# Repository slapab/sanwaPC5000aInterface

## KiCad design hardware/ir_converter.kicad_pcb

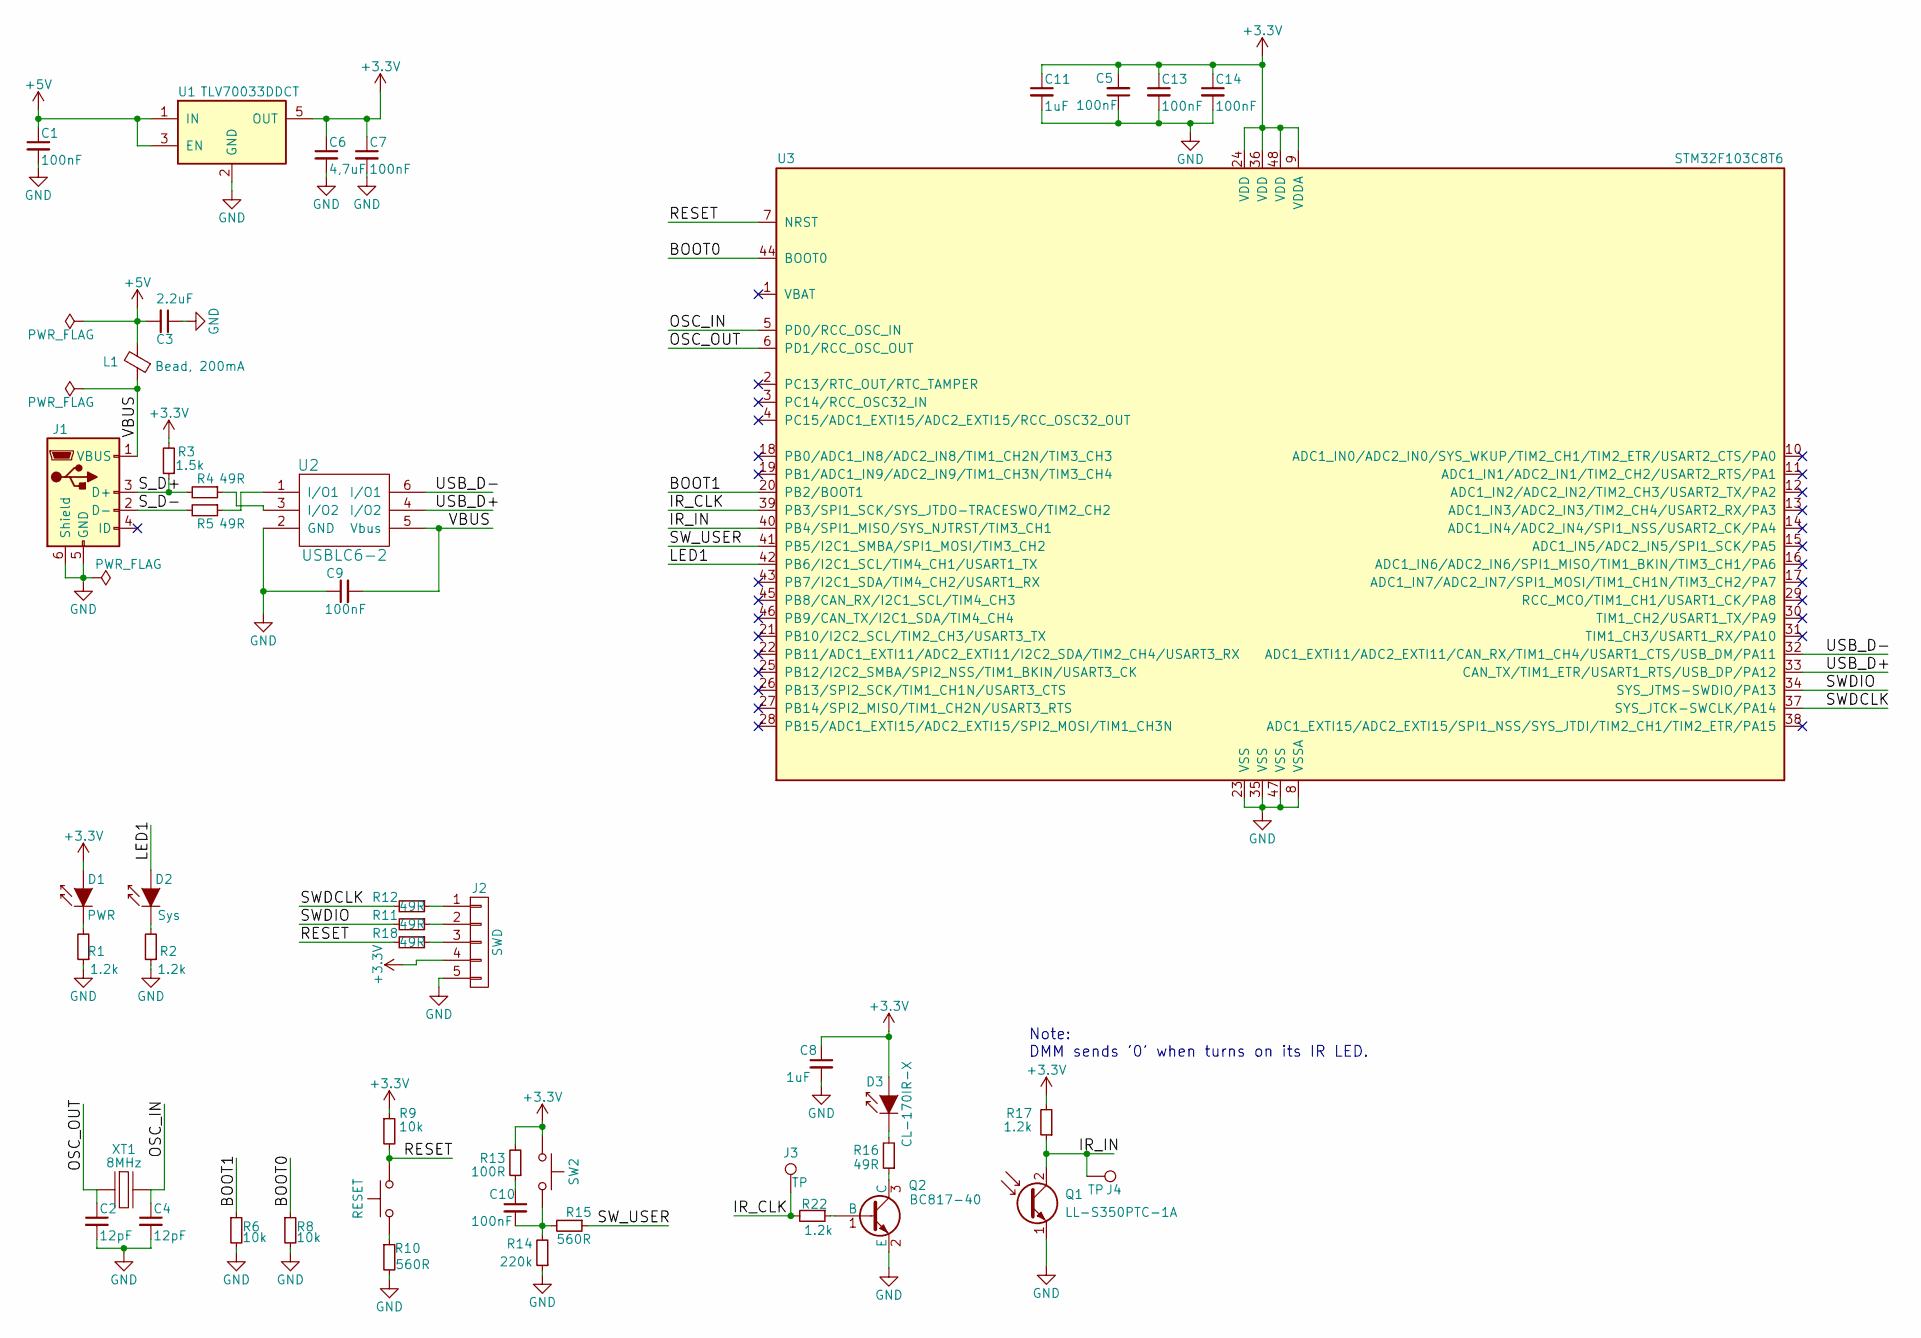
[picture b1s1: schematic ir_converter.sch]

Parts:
C1, C5, C7, C9, C10, C13, C14: 100nF; C_0603_HandSoldering
C2, C4: 12pF; C_0603_HandSoldering
C3: 2.2uF; C_0805_HandSoldering
C6: 4,7uF; C_0603_HandSoldering
C8, C11: 1uF; C_0603_HandSoldering
D1: PWR; LED_1206
D2: Sys; LED_1206
D3: CL-170IR-X; IR_LED_WIDE
J1: MX-47346-0001; USB_MICRO_MX-47346-0001
J2: SWD; Pin_Header_Straight_1x05_Pitch2.54mm
J3, J4: TP; Measurement_Point_Square-SMD-Pad_Small
L1: Bead, 200mA; L_1206_Handsoldering
Q1: LL-S350PTC-1A; IR_PHOTO_WIDE
Q2: BC817-40; SOT-23
R1, R2, R17, R22: 1.2k; R_0603_HandSoldering
R3: 1.5k; R_0603_HandSoldering
R4, R5, R11, R12, R16, R18: 49R; R_0603_HandSoldering
R6, R8, R9: 10k; R_0603_HandSoldering
R10, R15: 560R; R_0603_HandSoldering
R13: 100R; R_0603_HandSoldering
R14: 220k; R_0603_HandSoldering
SW1: RESET; SW_SPST_FSMSM
SW2: SW2; SW_SPST_FSMSM
U1: TLV70033DDCT; SOT-23-5
U2: USBLC6-2; SOT-23-6_Handsoldering
U3: STM32F103C8T6; LQFP-48_7x7mm_Pitch0.5mm
XT1: 8MHz; Crystal_SMD_HC49-SD

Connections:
+3V3: C5.2, C6.1, C7.1, C8.1, C11.1, C13.1, C14.1, D1.2 (A), D3.2 (A), J2.4, R3.2, R9.1, R13.2, R17.2, SW2.1, U1.5 (OUT), U3.9 (VDDA), U3.24 (VDD), U3.36 (VDD), U3.48 (VDD)
+5V: C1.1, C3.2, L1.2, U1.1 (IN), U1.3 (EN)
/BOOT0: R8.1, U3.44 (BOOT0)
/BOOT1: R6.1, U3.20 (PB2/BOOT1)
/IR_CLK: J3.1, R22.2, U3.39 (PB3/SPI1_SCK/SYS_JTDO-TRACESWO/TIM2_CH2)
/IR_IN: J4.1, Q1.2 (C), R17.1, U3.40 (PB4/SPI1_MISO/SYS_NJTRST/TIM3_CH1)
/LED1: D2.2 (A), U3.42 (PB6/I2C1_SCL/TIM4_CH1/USART1_TX)
/OSC_IN: C4.1, U3.5 (PD0/RCC_OSC_IN), XT1.2
/OSC_OUT: C2.1, U3.6 (PD1/RCC_OSC_OUT), XT1.1
/RESET: R9.2, R18.2, SW1.2, U3.7 (NRST)
/SWDCLK: R12.2, U3.37 (SYS_JTCK-SWCLK/PA14)
/SWDIO: R11.2, U3.34 (SYS_JTMS-SWDIO/PA13)
/SW_USER: R15.1, U3.41 (PB5/I2C1_SMBA/SPI1_MOSI/TIM3_CH2)
/S_D+: J1.3 (D+), R3.1, R4.2
/S_D-: J1.2 (D-), R5.2
/USB_D+: U2.4 (I/O2), U3.33 (CAN_TX/TIM1_ETR/USART1_RTS/USB_DP/PA12)
/USB_D-: U2.6 (I/O1), U3.32 (ADC1_EXTI11/ADC2_EXTI11/CAN_RX/TIM1_CH4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)
/VBUS: C9.2, J1.1 (VBUS), L1.1, U2.5 (Vbus)
GND: C1.2, C2.2, C3.1, C4.2, C5.1, C6.2, C7.2, C8.2, C9.1, C11.2, C13.2, C14.2, J1.5 (GND), J1.6 (Shield), J2.5, Q1.1 (E), Q2.2 (E), R1.1, R2.1, R6.2, R8.2, R10.2, R14.1, U1.2 (GND), U2.2 (GND), U3.8 (VSSA), U3.23 (VSS), U3.35 (VSS), U3.47 (VSS)
unnamed: C10.1, R13.1
unnamed: C10.2, R14.2, R15.2, SW2.2
unnamed: D1.1 (K), R1.2
unnamed: D2.1 (K), R2.2
unnamed: D3.1 (K), R16.2
unnamed: J2.1, R12.1
unnamed: J2.2, R11.1
unnamed: J2.3, R18.1
unnamed: Q2.1 (B), R22.1
unnamed: Q2.3 (C), R16.1
unnamed: R4.1, U2.3 (I/O2)
unnamed: R5.1, U2.1 (I/O1)
unnamed: R10.1, SW1.1

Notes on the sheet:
Note: DMM sends '0' when turns on its IR LED.

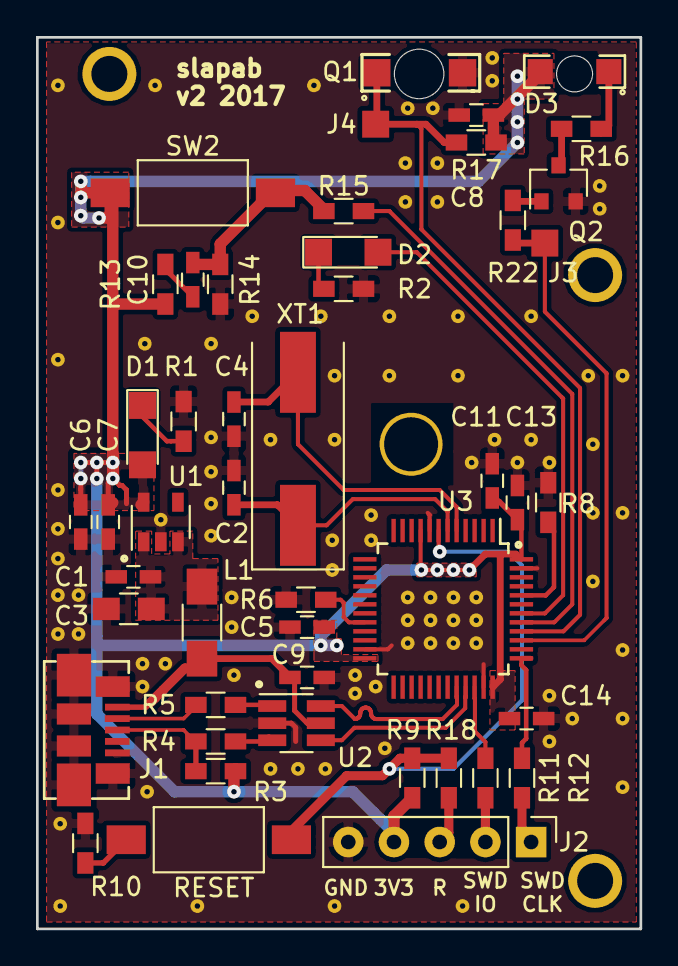
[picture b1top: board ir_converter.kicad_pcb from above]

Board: 2 copper layers, 33.5 x 49.5 mm, 47 parts (0 on the bottom side), 32 nets.

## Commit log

2017-03-14 libopencm3 submodule
2017-03-14 Added initial files and configurations.
2017-03-16 Updated makefiles to to use openocd to flash firmware.
2017-03-17 Added eclipse (nenon) project to the application sources. Started implementation of conversion IR raw data to the BM packets.
2017-03-20 Implementation...
2017-03-21 Added Unity framewor for unit testing. Created directory for application's tests. Updated bm_dmm_protocol.c/.h files to compile unit-tests project.
2017-03-22 Added few tests. Fixed calculating checksum in brymen protocol.
2017-03-22 Added all required tests for bm_dmm_protocol.c/.h. And fixed some issues.
2017-03-23 Moved few macros to the header. Added function to check for data request command and proper unit tests.
2017-03-24 Further implementation.
2017-03-26 Inserting read bits from IR receiver into buffer. Not tested yet.
2017-03-28 Moved usb-cdc configuration to new source files. Created one function to initialize systick. Added sources to compilation.
2017-04-07 Added first version of hardware
2017-04-08 Changed ground plane clearance
2017-04-09 Upated usbdfu_bootloader for hardware v0.1
2017-04-09 Updated project to work on hardware v0.1. Also fixes some bugs.
2017-04-09 testing
2017-04-23 Fixed setting custom callback for usb-rx event. First attemption to use timer to generate the CLK signal and collect data on falling edge. Code NEEDS cleaning!
2017-05-02 Added constant for USB_CDC buffer size.
2017-05-02 Added into makefile code that defines on which hardware version the code will be compiled. Version that will be used is defined by setting variable "USING_INTERFACE_VER" in makefile or as an argument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
2017-05-02 Cleanup and updating code to take use of hardware version informations.
2017-05-02 Cleanup
2017-05-03 Added simple software timers implementation
2017-05-03 ir-interface - the non-blocking reading data uses software timer to prevent hanging out when DMM didn't respond for data request signal.
2017-05-03 Added npn tranistor to drive the IR LED.
2017-05-23 Added bug fixes on schematic. Redesigning PCB.
2017-05-24 Elements arrangement.
2017-05-25 Almost done.
2017-05-25 Custom footprints for IR LED and IR phototransistor
2017-05-26 New PCB is ready.
2017-05-26 Generated documentation files
2017-05-26 Added schematic
2017-07-02 Prepared for fabrication
2017-11-12 Resizing mouting holes
2017-11-12 Changing clock configuration to use 8MHz external
2017-11-12 Updated code to work with version 2 of hardware.
